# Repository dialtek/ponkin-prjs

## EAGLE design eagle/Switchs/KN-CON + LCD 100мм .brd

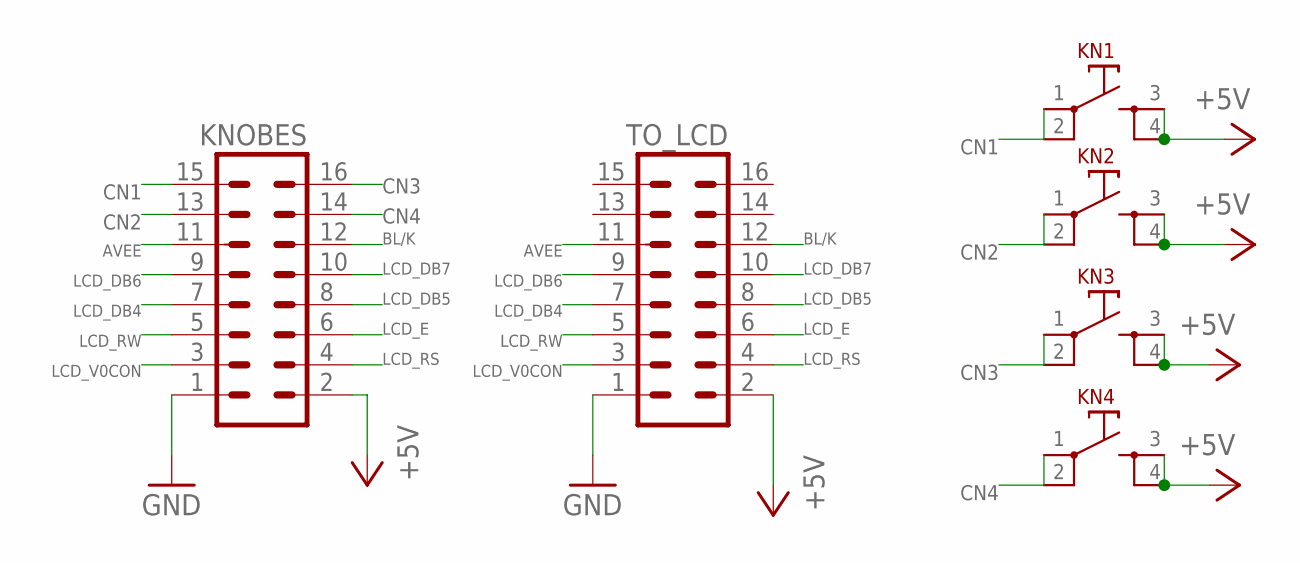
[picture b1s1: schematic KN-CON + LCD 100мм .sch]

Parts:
KN1, KN2, KN3, KN4: LZQ-KN
KNOBES: ML16
TO_LCD: ML16

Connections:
+5V: KN1.3, KN1.4, KN2.3, KN2.4, KN3.3, KN3.4, KN4.3, KN4.4, KNOBES.2, TO_LCD.2
AVEE: KNOBES.11, TO_LCD.11
BL/K: KNOBES.12, TO_LCD.12
CN1: KN1.1, KN1.2, KNOBES.15
CN2: KN2.1, KN2.2, KNOBES.13
CN3: KN3.1, KN3.2, KNOBES.16
CN4: KN4.1, KN4.2, KNOBES.14
GND: KNOBES.1, TO_LCD.1
LCD_DB4: KNOBES.7, TO_LCD.7
LCD_DB5: KNOBES.8, TO_LCD.8
LCD_DB6: KNOBES.9, TO_LCD.9
LCD_DB7: KNOBES.10, TO_LCD.10
LCD_E: KNOBES.6, TO_LCD.6
LCD_RS: KNOBES.4, TO_LCD.4
LCD_RW: KNOBES.5, TO_LCD.5
LCD_V0CON: KNOBES.3, TO_LCD.3

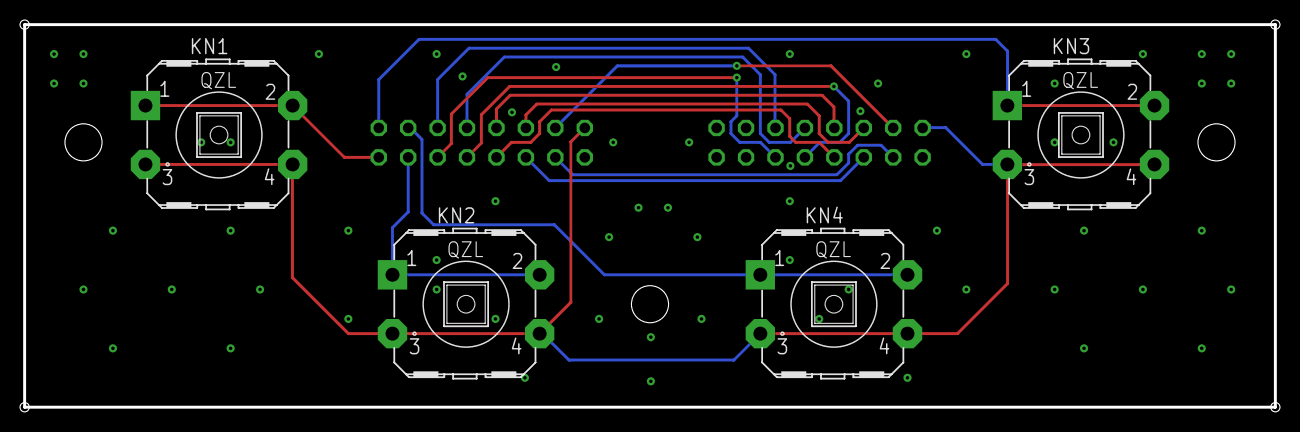
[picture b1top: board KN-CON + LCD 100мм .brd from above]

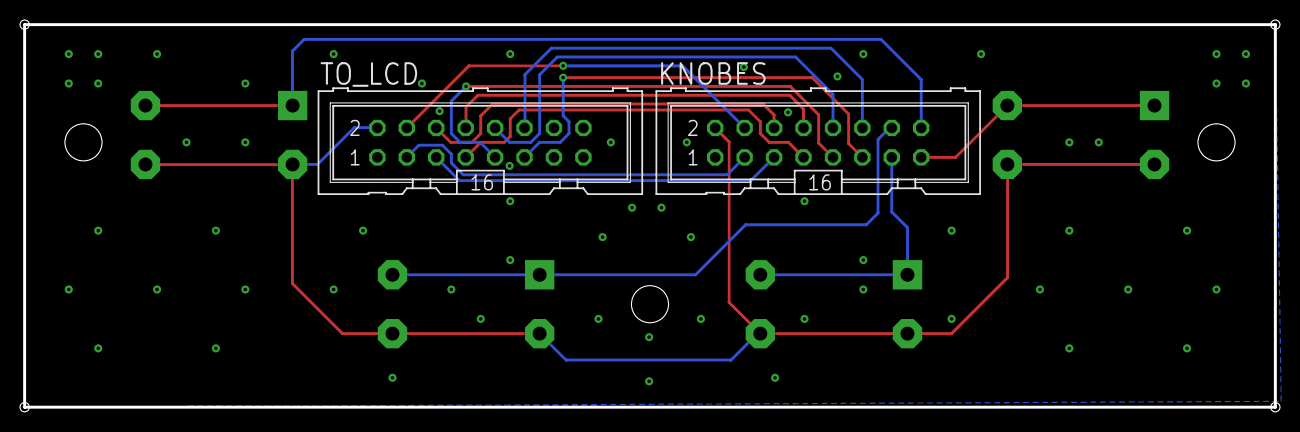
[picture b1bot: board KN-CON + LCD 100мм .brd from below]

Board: 2 copper layers, 108.0 x 33.0 mm, 6 parts (2 on the bottom side), 16 nets.

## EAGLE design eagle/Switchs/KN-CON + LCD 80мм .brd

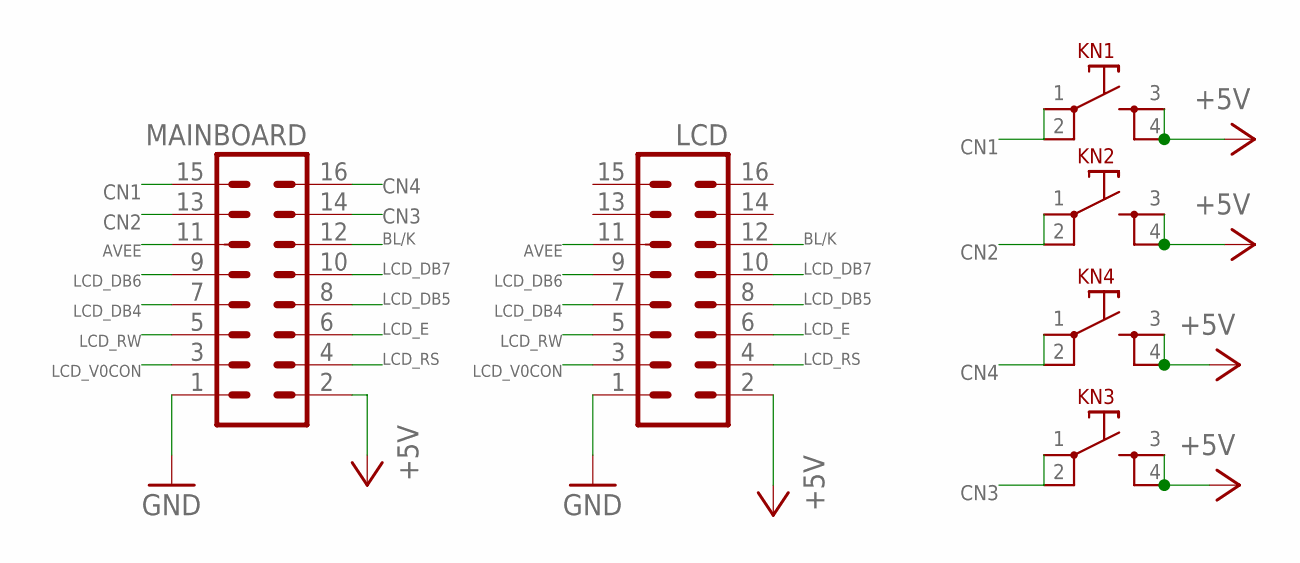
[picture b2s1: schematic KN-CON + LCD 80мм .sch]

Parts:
KN1, KN2, KN3, KN4: LZQ-KN
LCD: ML16
MAINBOARD: ML16

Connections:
+5V: KN1.3, KN1.4, KN2.3, KN2.4, KN3.3, KN3.4, KN4.3, KN4.4, LCD.2, MAINBOARD.2
AVEE: LCD.11, MAINBOARD.11
BL/K: LCD.12, MAINBOARD.12
CN1: KN1.1, KN1.2, MAINBOARD.15
CN2: KN2.1, KN2.2, MAINBOARD.13
CN3: KN3.1, KN3.2, MAINBOARD.14
CN4: KN4.1, KN4.2, MAINBOARD.16
GND: LCD.1, MAINBOARD.1
LCD_DB4: LCD.7, MAINBOARD.7
LCD_DB5: LCD.8, MAINBOARD.8
LCD_DB6: LCD.9, MAINBOARD.9
LCD_DB7: LCD.10, MAINBOARD.10
LCD_E: LCD.6, MAINBOARD.6
LCD_RS: LCD.4, MAINBOARD.4
LCD_RW: LCD.5, MAINBOARD.5
LCD_V0CON: LCD.3, MAINBOARD.3

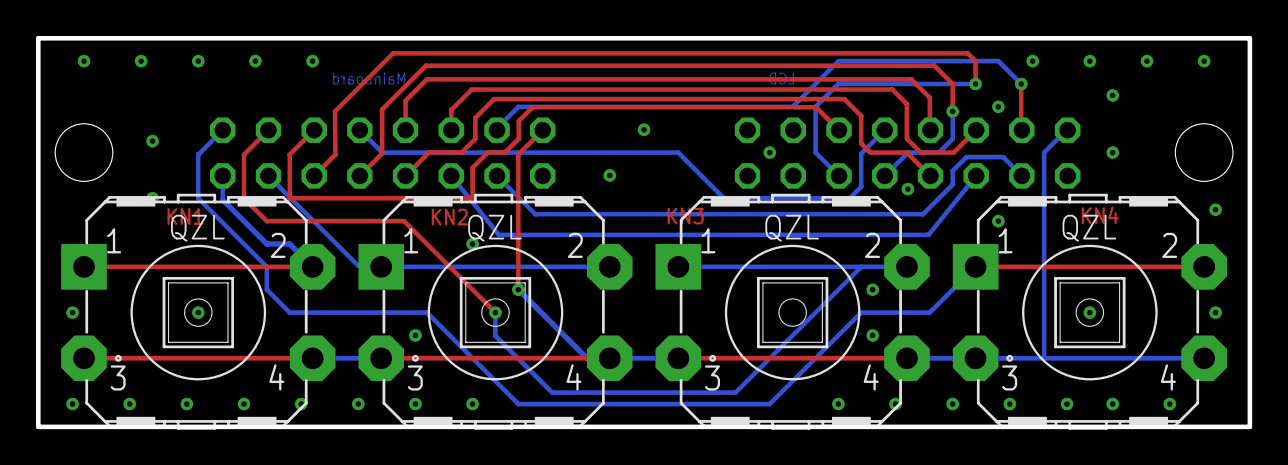
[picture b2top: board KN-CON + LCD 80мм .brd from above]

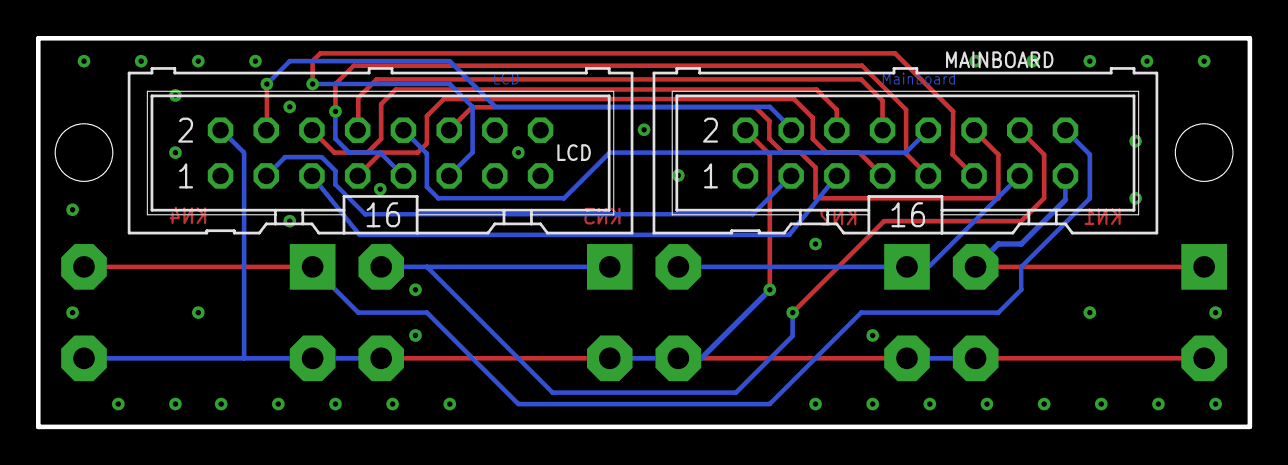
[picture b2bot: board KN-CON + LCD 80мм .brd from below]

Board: 2 copper layers, 67.3 x 21.6 mm, 6 parts (2 on the bottom side), 16 nets.

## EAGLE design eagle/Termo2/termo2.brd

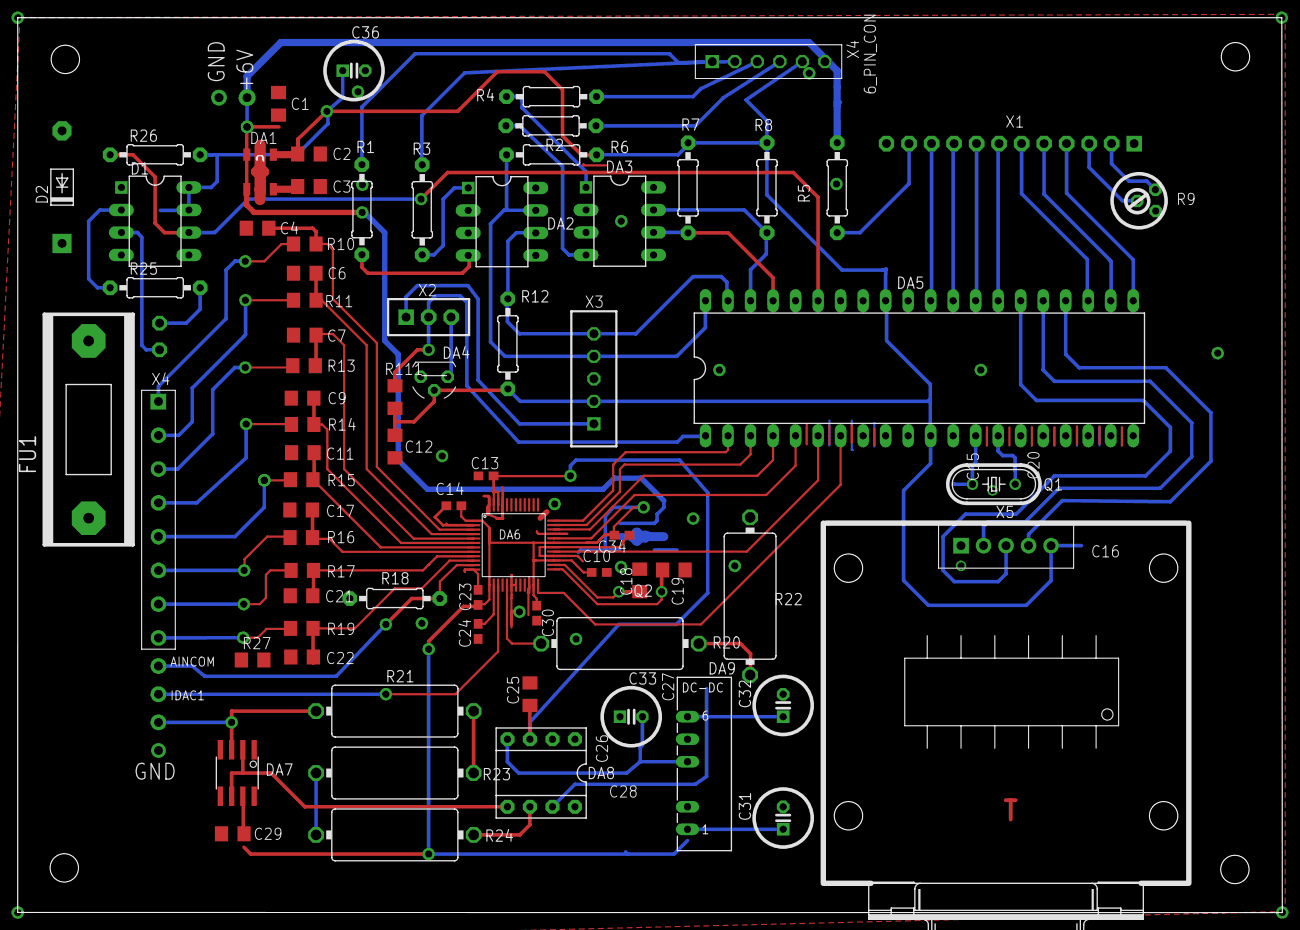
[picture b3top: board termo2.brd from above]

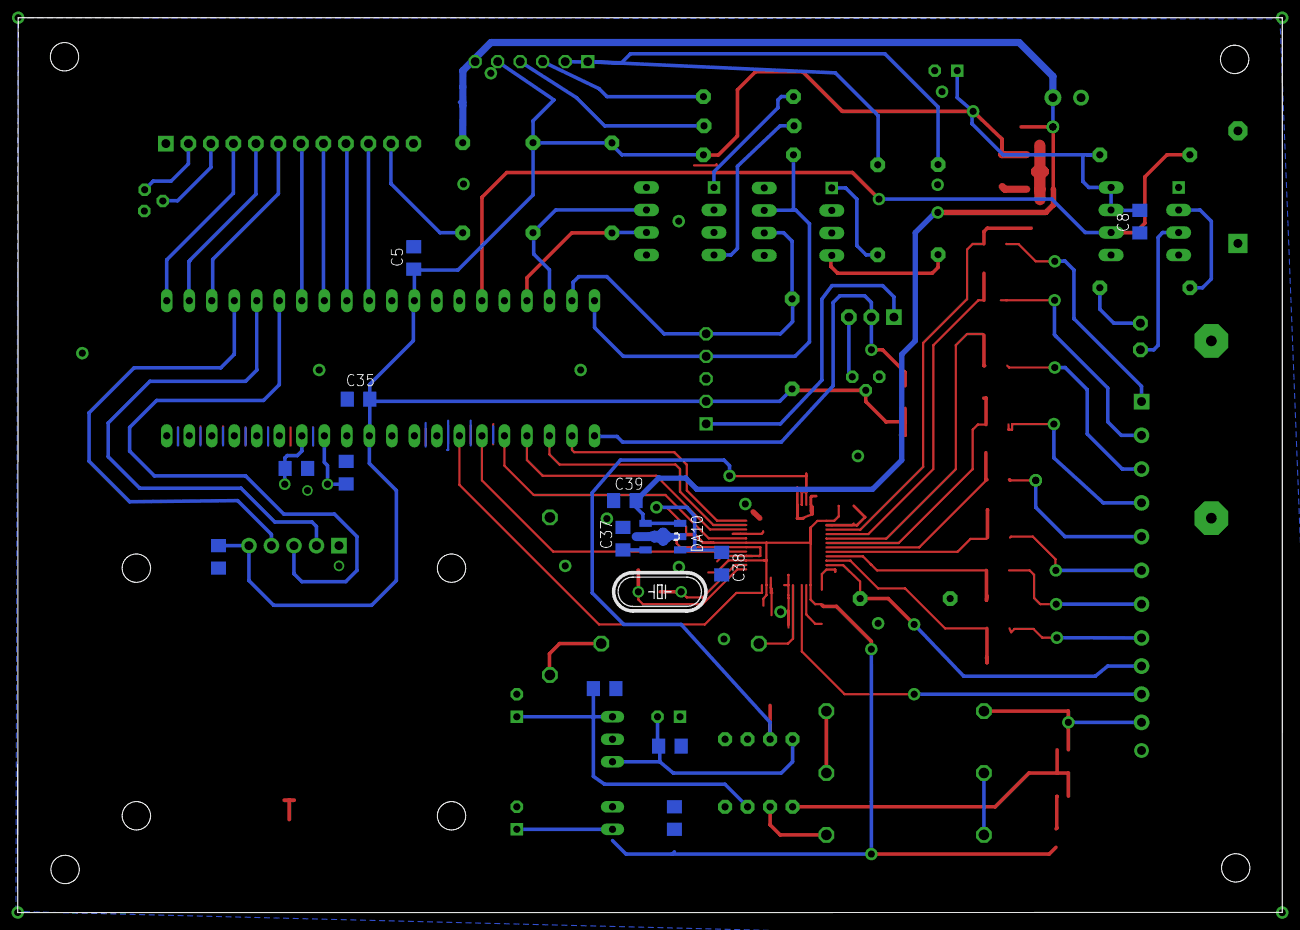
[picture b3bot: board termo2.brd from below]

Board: 2 copper layers, 142.7 x 101.0 mm, 90 parts (14 on the bottom side), 74 nets.

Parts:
8_PIN_1: 8_PIN_CON
C1, C8, C12, C16, C25, C26, C27, C28, C29, C35, C39: 0.1u; C0805D
C2, C38: 1u; C0805D
C3, C37: 0.01u; C0805D
C4: 1n; C0805D
C5, C6, C7, C9, C11, C17, C18, C19, C21, C22: C0805D
C10: C0603
C13, C14, C23, C30, C34: 0.1u; C0603
C15, C20: 12p; C0805D
C24: 1n; C0603
C31, C32, C33, C36: C100MILX6X12
D1: 6N137; DIL08
D2: 1N5061; DO41-10
DA1, DA10: NJM2880; SOT89-5
DA2, DA3: CNY74-H; CNY_DIP8
DA4: DS1811; TO92-60
DA5: PIC18F4320_40; DIL40
DA6: ADS1216ADS1216; ADS1216_PAC
DA7: OPA340U; SO08
DA8: INA128P; DIL08
DA9: NMA
FU1: FUSE5X20
P1, P2: 1_PIN_CON
Q1, Q2: HC49/S
R1, R2, R3, R4, R25: 330; 0207/10
R5, R26: 1k; 0207/10
R6, R7, R8, R12: 4k7; 0207/10
R9: RTRIM3329H
R10: 1k; R0805D
R11, R13, R14, R15, R16, R17, R19: R0805D
R18: 100k; 0207/10
R20, R22: 100k; V235/17
R21, R23, R24: 250k; V235/17
R27, R111: 10k; R0805D
X1: WINSTAR16X4_12
X2: PLC-3PIN
X3: PLC-5PIN
X4: 6_PIN_CON; 6_IN_PINS
X5: KM_RS_232

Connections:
1: DA5.1, R111.P$1, X2.P$2
+5V: C2.1, C5.2, C8.2, C12.2, C16.2, C28.1, C29.1, C31.PLUS, C35.1, C36.PLUS, D1.7, D1.8, DA1.4, DA4.2, DA5.11, DA5.32, DA7.7, DA9.1, R6.2, R7.2, R8.2, R9.2, R12.2, R26.2, R111.P$2, X1.P$2, X3.P$2, X4.P$5, X5.5
+5V_AVDD: C10.2, C14.1, C23.2, C30.1, C34.2, C38.1, DA6.1, DA6.13, DA6.23, DA6.27, DA6.31, DA10.4
+6V: C1.2, C39.2, D2.C, DA1.1, DA1.5, DA10.1, DA10.5, FU1.P$2, R5.1
AINCOM: DA6.11, R18.1
DB4: DA5.27, X1.P$7
DB5: DA5.28, X1.P$8
DB6: DA5.29, X1.P$9
DB7: DA5.30, X1.P$10
DRDY: DA5.5, DA6.32
DSYNC: DA5.6, DA6.29
D_IN: DA5.3, DA6.35
D_OUT: DA5.2, DA6.36
E: DA5.23, X1.P$6
IN1.1: C4.1, DA6.3, R10.P$1
IN1.2: C6.1, DA6.4, R11.P$1
IN2.1: C7.1, DA6.5, R13.P$1
IN2.2: C9.1, DA6.6, R14.P$1
IN3.1: C11.1, DA6.7, R15.P$1
IN3.2: C17.1, DA6.8, R16.P$1
IN4.1: C21.1, DA6.9, R17.P$1
IN4.2: C22.1, DA6.10, R19.P$1
INA_OUT: DA7.3, R21.1
K2: R1.2, X4.P$2
K3: R4.1, X4.P$3
K4: R2.2, X4.P$4
KN1,PGD: DA2.7, DA5.40, R6.1, X3.P$4
KN2,PGC: DA2.6, DA5.39, R12.1, X3.P$5
KN3: DA3.7, DA5.38, R8.1
KN4: DA3.6, DA5.37, R7.1
MCLR: X2.P$1, X3.P$1
unnamed: C15.2, DA5.13, Q1.1
unnamed: C20.2, DA5.14, Q1.2
unnamed: DA2.4, R1.1
unnamed: C3.1, DA1.3
unnamed: C24.2, DA6.14
unnamed: DA4.1, X2.P$3
unnamed: C19.2, DA6.25, Q2.2
unnamed: C18.2, DA6.26, Q2.1
unnamed: 8_PIN_1.P$6, R16.P$2
unnamed: 8_PIN_1.P$1, R10.P$2
unnamed: 8_PIN_1.P$2, R11.P$2
unnamed: 8_PIN_1.P$7, R17.P$2
unnamed: DA3.1, R4.2
unnamed: 8_PIN_1.P$8, R19.P$2, R27.P$1
unnamed: DA3.4, R2.1
unnamed: R5.2, X1.P$11
unnamed: 8_PIN_1.P$5, R15.P$2
unnamed: C27.1, C32.PLUS, DA8.7, DA9.6
unnamed: 8_PIN_1.P$3, R13.P$2
unnamed: 8_PIN_1.P$4, R14.P$2
unnamed: DA7.2, DA7.6, DA8.5
unnamed: DA8.6, R24.2
unnamed: C26.1, C33.MINUS, DA8.4, DA9.4
unnamed: DA5.26, X5.3
unnamed: DA5.25, X5.2
unnamed: DA5.24, X5.4
unnamed: R23.2, R24.1
unnamed: R21.2, R23.1
unnamed: DA6.17, R20.1
unnamed: R20.2, R22.1
unnamed: C37.1, DA10.3
unnamed: D1.6, DA5.35, R26.1
unnamed: D1.2, R25.1
unnamed: D1.3, P2.P$1
unnamed: P1.P$1, R25.2
PE: C1.1, C2.2, C3.2, C4.2, C5.1, C6.2, C7.2, C8.1, C9.2, C10.1, C11.2, C12.1, C13.2, C14.2, C15.1, C16.1, C17.2, C18.1, C19.1, C20.1, C21.2, C22.2, C23.1, C24.1, C25.2, C26.2, C27.2, C28.2, C29.2, C30.2, C31.MINUS, C32.MINUS, C33.PLUS, C34.1, C35.2, C36.MINUS, C37.2, C38.2, C39.1, D1.5, D2.A, DA1.2, DA1.21, DA2.2, DA2.3, DA2.5, DA2.8, DA3.2, DA3.3, DA3.5, DA3.8, DA4.3, DA5.12, DA5.31, DA6.2, DA6.12, DA6.18, DA6.19, DA6.20, DA6.21, DA6.22, DA6.28, DA6.30, DA6.45, DA6.48, DA7.4, DA8.2, DA9.2, DA9.5, DA10.2, DA10.21, R9.1, R18.2, R22.2, R27.P$2, X1.P$1, X1.P$12, X3.P$3, X4.P$6, X5.1
R15: DA2.1, R3.2
REF: C13.1, C25.1, DA6.46, DA6.47, DA8.3
RESET: DA5.7, DA6.24
RS: DA5.21, X1.P$4
RW: DA5.22, X1.P$5
SCLK: DA5.4, DA6.34
V0CON: R9.3, X1.P$3

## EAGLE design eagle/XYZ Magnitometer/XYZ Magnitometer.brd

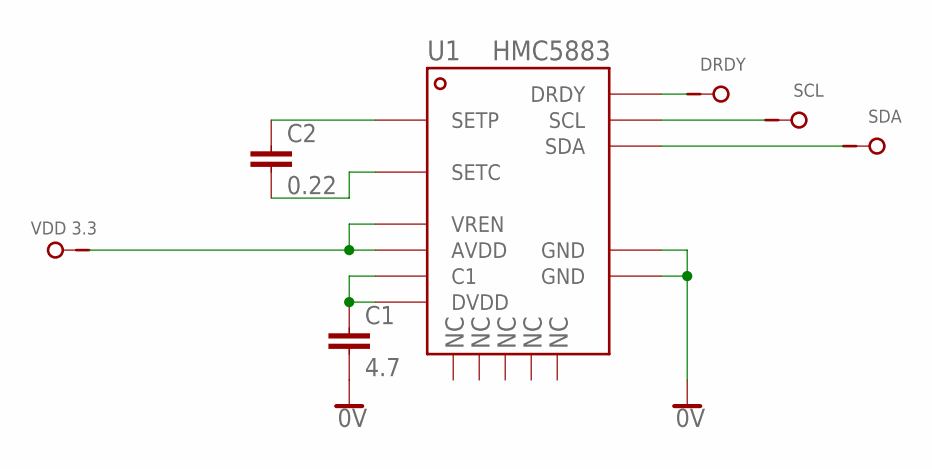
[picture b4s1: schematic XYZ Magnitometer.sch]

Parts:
C1: 4.7; C1206K
C2: 0.22; C0805K
P1: SDA; 1_PIN_PLANAR
P2: VDD 3.3; 1_PIN_PLANAR
P3: SCL; 1_PIN_PLANAR
P5: DRDY; 1_PIN_PLANAR
U1: HMC5883; QFN16-4X4

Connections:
0V: C1.2, U1.P$9 (GND), U1.P$11 (GND)
1: U1.P$3 (1)
2: U1.P$4 (2)
3: U1.P$5 (3)
4: U1.P$6 (4)
5: U1.P$7 (5)
unnamed: C1.1, U1.P$10 (C1), U1.P$13 (DVDD)
unnamed: C2.1, U1.P$8 (SETP)
unnamed: C2.2, U1.P$12 (SETC)
unnamed: P2.P$1, U1.P$2 (AVDD), U1.P$14 (VREN)
unnamed: P3.P$1, U1.P$1 (SCL)
unnamed: P1.P$1, U1.P$16 (SDA)
unnamed: P5.P$1, U1.P$15 (DRDY)

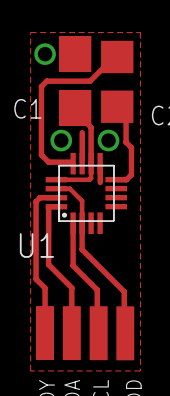
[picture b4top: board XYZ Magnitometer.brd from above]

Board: 2 copper layers, 7 parts (0 on the bottom side), 8 nets.

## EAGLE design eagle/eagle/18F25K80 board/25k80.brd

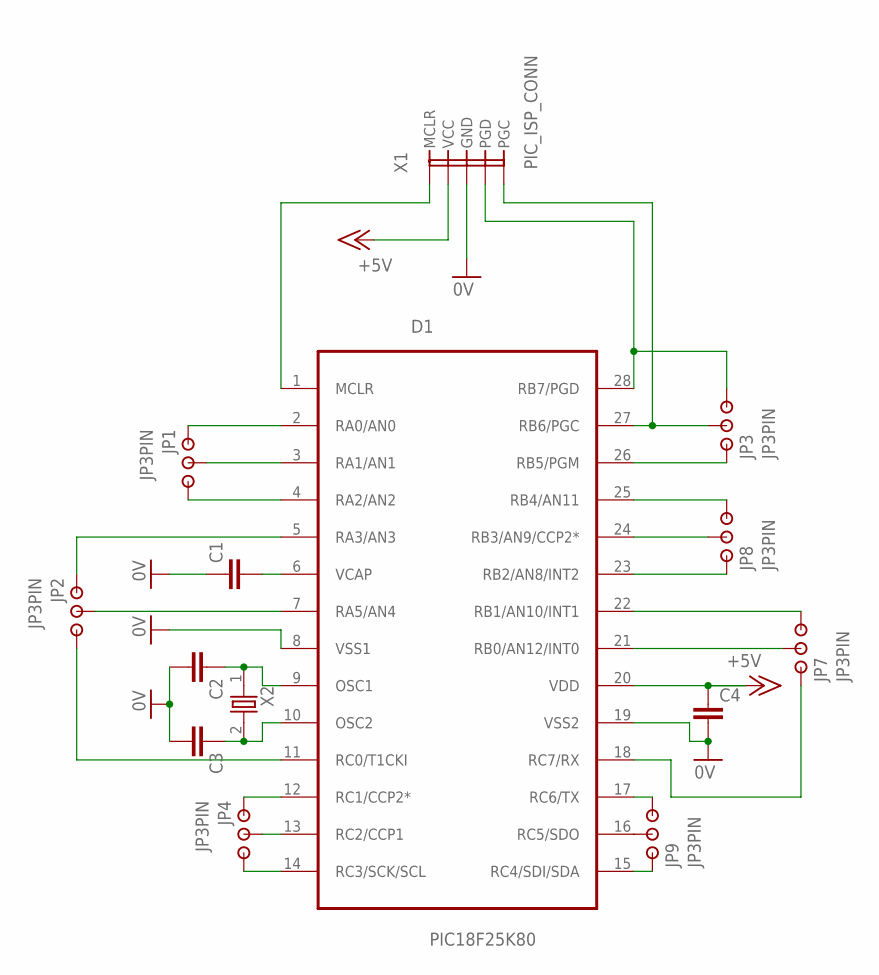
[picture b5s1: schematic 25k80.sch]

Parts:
C1, C2, C3, C4: C0805; C0805D
D1: PIC18F25K80; SO-28W
JP1, JP2, JP3, JP4, JP7, JP8, JP9: JP3PIN; PLC-3PIN
X1: PIC_ISP_CONN; PLC-5PIN
X2: HC49/S

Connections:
0V: C1.1, C2.2, C3.2, C4.2, D1.8 (VSS1), D1.19 (VSS2), X1.P$3 (GND)
+5V: C4.1, D1.20 (VDD), X1.P$2 (VCC)
unnamed: D1.28 (RB7/PGD), JP3.P$3, X1.P$4 (PGD)
unnamed: D1.27 (RB6/PGC), JP3.P$2, X1.P$5 (PGC)
unnamed: D1.1 (MCLR), X1.P$1 (MCLR)
unnamed: C1.2, D1.6 (VCAP)
unnamed: D1.2 (RA0/AN0), JP1.P$1
unnamed: D1.3 (RA1/AN1), JP1.P$2
unnamed: D1.4 (RA2/AN2), JP1.P$3
unnamed: D1.5 (RA3/AN3), JP2.P$1
unnamed: D1.7 (RA5/AN4), JP2.P$2
unnamed: D1.25 (RB4/AN11), JP8.P$3
unnamed: D1.26 (RB5/PGM), JP3.P$1
unnamed: C2.1, D1.9 (OSC1), X2.1
unnamed: C3.1, D1.10 (OSC2), X2.2
unnamed: D1.24 (RB3/AN9/CCP2*), JP8.P$2
unnamed: D1.23 (RB2/AN8/INT2), JP8.P$1
unnamed: D1.22 (RB1/AN10/INT1), JP7.P$3
unnamed: D1.21 (RB0/AN12/INT0), JP7.P$2
unnamed: D1.11 (RC0/T1CKI), JP2.P$3
unnamed: D1.18 (RC7/RX), JP7.P$1
unnamed: D1.16 (RC5/SDO), JP9.P$2
unnamed: D1.17 (RC6/TX), JP9.P$3
unnamed: D1.15 (RC4/SDI/SDA), JP9.P$1
unnamed: D1.14 (RC3/SCK/SCL), JP4.P$3
unnamed: D1.13 (RC2/CCP1), JP4.P$2
unnamed: D1.12 (RC1/CCP2*), JP4.P$1

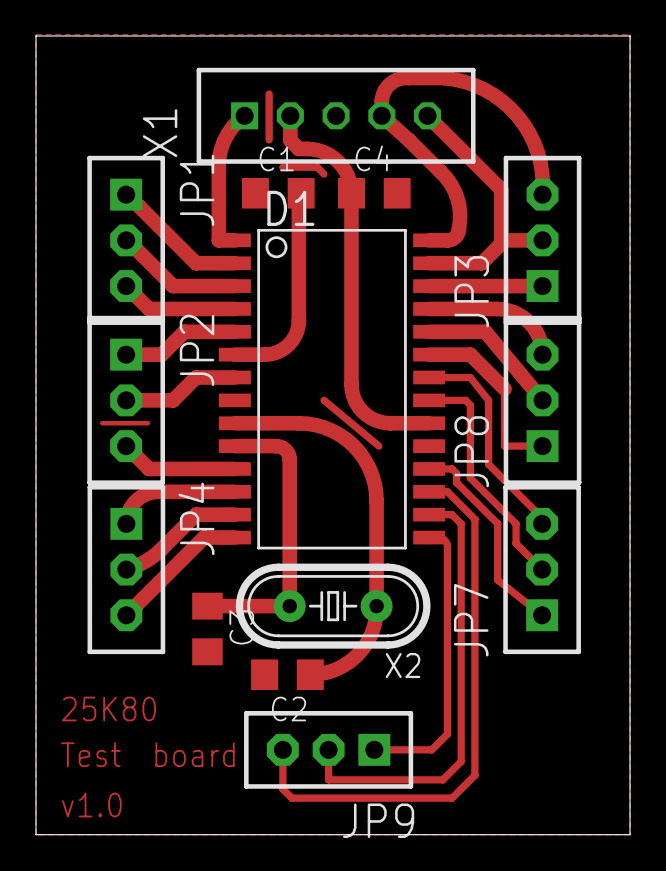
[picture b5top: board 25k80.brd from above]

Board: 2 copper layers, 33.0 x 44.4 mm, 14 parts (0 on the bottom side), 27 nets.

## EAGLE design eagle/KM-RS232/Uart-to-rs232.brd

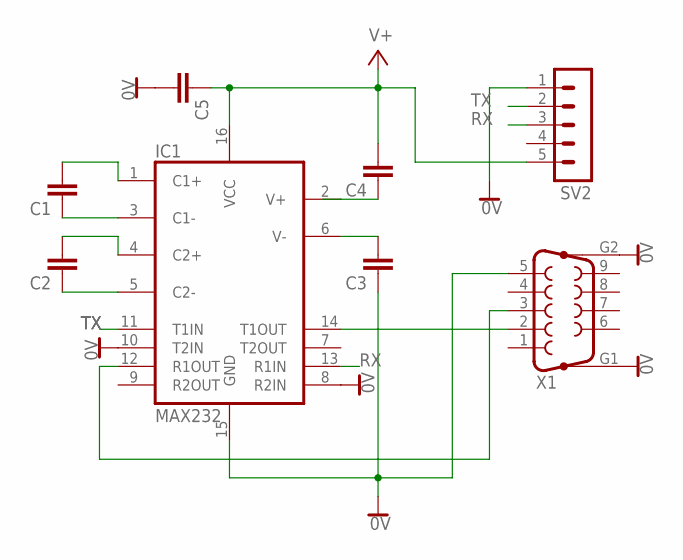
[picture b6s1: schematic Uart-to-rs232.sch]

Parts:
C1, C2, C3, C4, C5: C0805; C0805D
IC1: MAX232; DIL16
SV2: MA05-1
X1: F09HP

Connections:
0V: C3.1, C5.2, IC1.8 (R2IN), IC1.10 (T2IN), IC1.15 (GND), SV2.1, X1.5, X1.G1, X1.G2
+5V: C4.2, C5.1, IC1.16 (VCC), SV2.5
unnamed: IC1.14 (T1OUT), X1.2
unnamed: C1.2, IC1.1 (C1+)
unnamed: C1.1, IC1.3 (C1-)
unnamed: C2.2, IC1.4 (C2+)
unnamed: C2.1, IC1.5 (C2-)
unnamed: C3.2, IC1.6 (V-)
unnamed: C4.1, IC1.2 (V+)
unnamed: IC1.12 (R1OUT), X1.3
RX: IC1.13 (R1IN), SV2.3
TX: IC1.11 (T1IN), SV2.2

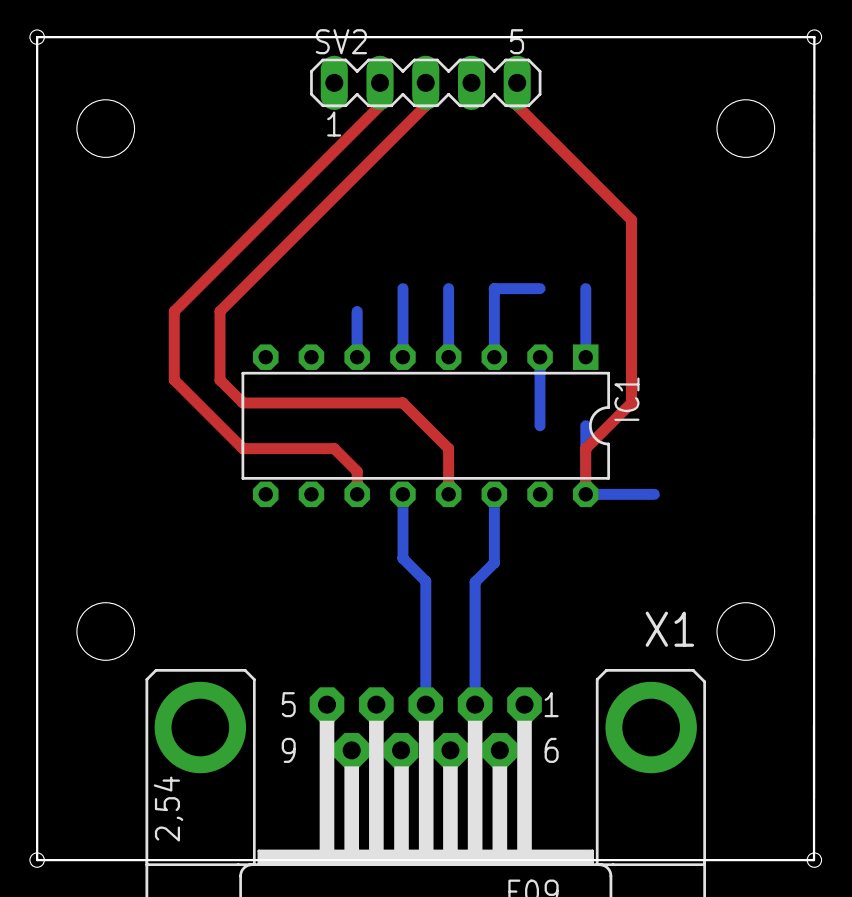
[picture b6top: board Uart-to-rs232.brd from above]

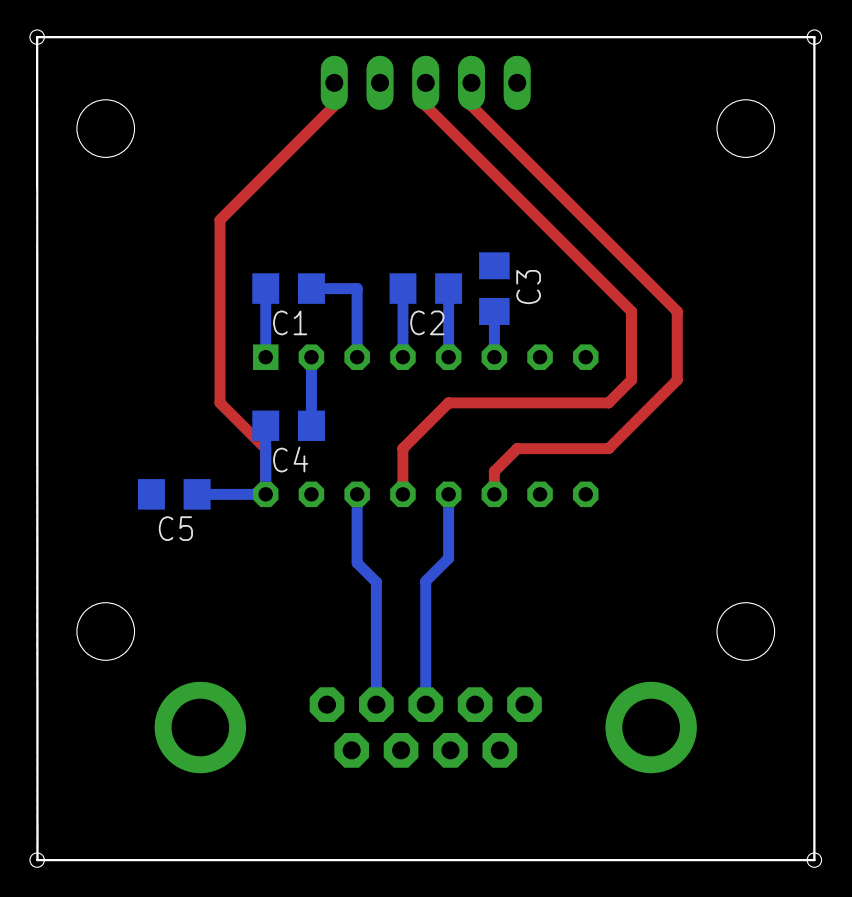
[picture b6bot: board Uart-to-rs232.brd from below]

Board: 2 copper layers, 43.2 x 45.7 mm, 8 parts (5 on the bottom side), 12 nets.

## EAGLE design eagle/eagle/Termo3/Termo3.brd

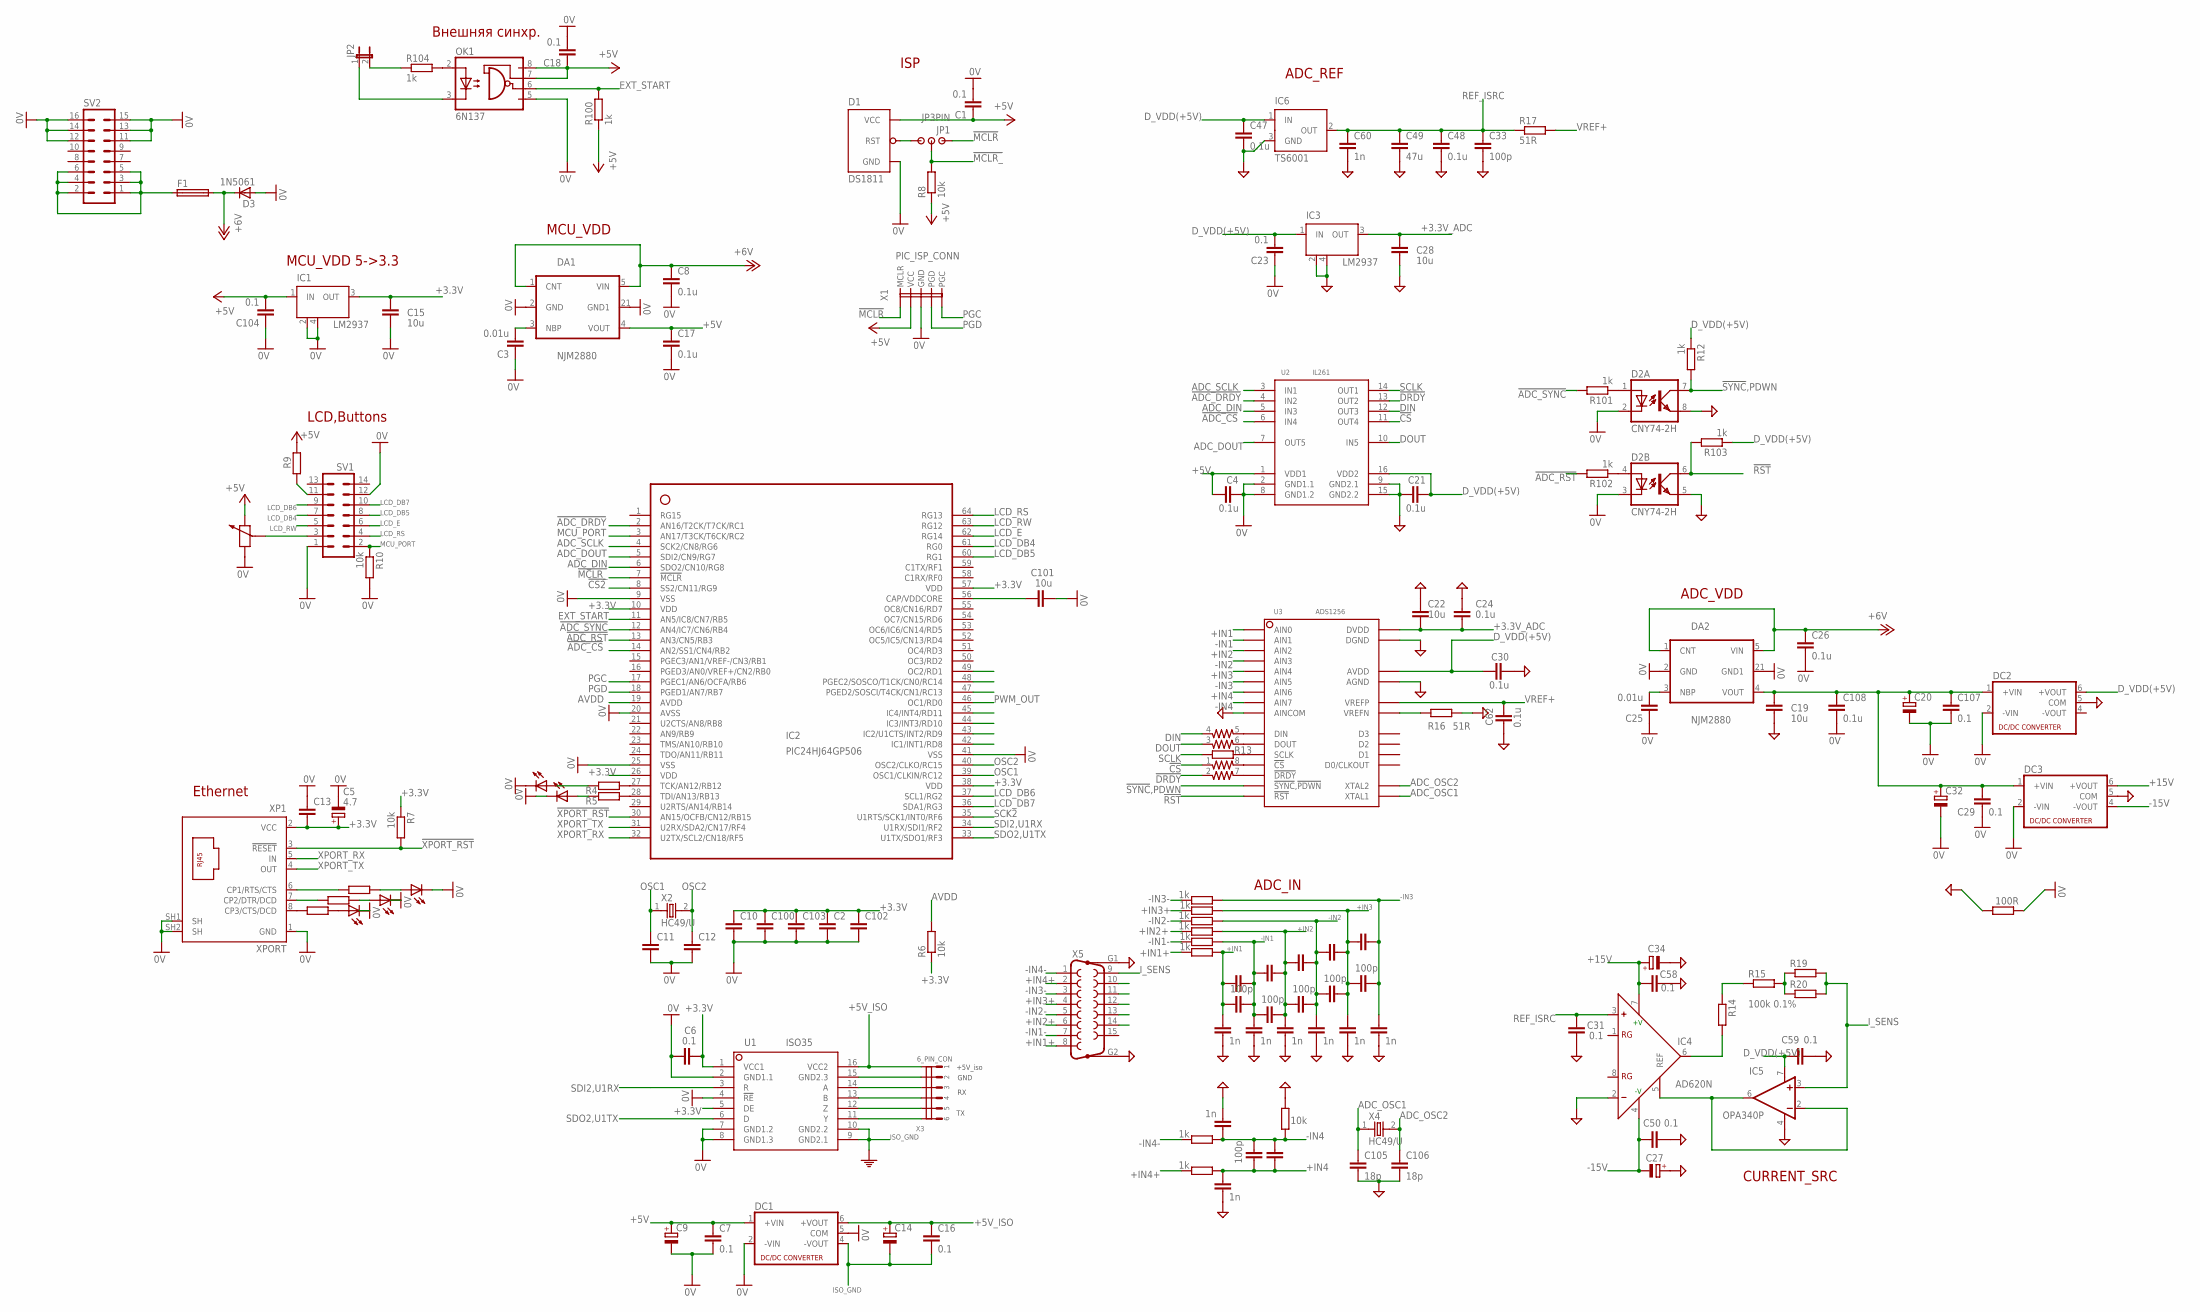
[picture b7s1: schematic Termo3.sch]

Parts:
C1, C6, C7, C16, C18, C23, C29, C31, C50, C58, C59, C104, C107: 0.1; C0805D
C2, C10, C11, C12, C13, C100, C102, C103: C0805; C0805D
C3, C25: 0.01u; C0805D
C4, C8, C17, C21, C24, C26, C30, C47, C48, C62, C108: 0.1u; C0805D
C5: 4.7; C100MILX6X12
C9, C14, C20, C27, C32, C34: C100MFX25V; C100MILX6X12
C15, C19, C22, C28, C101: 10u; C0805D
C33, C35, C36, C37, C38, C39, C40: 100p; C0805D
C41, C42, C43, C44, C45, C46, C51, C52, C53, C54, C55, C56, C57, C60, C61: 1n; C0805D
C49: 47u; C0805D
C105, C106: 18p; C0805D
D1: DS1811; TO92-60
D2: CNY74-2H; DIL08
D3: 1N5061; DO41-10
DA1, DA2: NJM2880; SOT89-5
DC1, DC2, DC3: NMA
F1: TE5
HL1, HL2, HL3, HL4, HL5: LED3MM
IC1, IC3: LM2937; SOT223
IC2: PIC24HJ64GP506; TQFP64-10X10
IC4: AD620N; DIL08
IC5: OPA340P; DIL08
IC6: TS6001; SOT23
JP1: JP3PIN; PLC-3PIN
JP2: JP1E; JP1
OK1: 6N137; DIL08
POT1: RTRIM3329H
R1, R2, R3, R12, R21, R22, R23, R24, R25, R26, R27, R28, R100, R101, R102, R103, R104: 1k; R0805D
R4, R5, R13, R16, R17: 51R; R0805D
R6, R7, R8, R10, R18: 10k; R0805D
R9, R14, R19, R20: MLT025"; 0207/10
R11: 100R; R0805D
R15: 100k 0.1%; 0207/10
RN1: 742-8_SNS; 742-8NS
SV1: ML14
SV2: MA08-2W
U1: ISO35; ISO35_SOIC16
U2: IL261; SOIC-16
U3: ADS1256; PCM2705-TSSOP28
X1: PIC_ISP_CONN; PLC-5PIN
X2, X4: HC49/U; HC49U-V
X3: 6_PIN_CON; 6_IN_PINS
X5: F15HP
XP1: XPORT

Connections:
0V: C1.2, C2.2, C3.1, C4.2, C5.MINUS (-), C6.1, C7.2, C8.2, C9.MINUS (-), C10.2, C11.2, C12.2, C13.1, C15.1, C17.2, C18.2, C20.MINUS (-), C23.1, C25.1, C26.2, C29.1, C32.MINUS (-), C100.2, C101.2, C102.2, C103.2, C104.1, C107.2, C108.2, D1.3 (GND), D2.2 (C), D2.3 (C), D3.A, DA1.2 (GND), DA1.21 (GND1), DA2.2 (GND), DA2.21 (GND1), DC1.2 (-VIN), DC1.5 (COM), DC2.2 (-VIN), DC3.2 (-VIN), HL1.K (C), HL2.K (C), HL3.K (C), HL4.K (C), HL5.K (C), IC1.2 (GND), IC1.4 (GND), IC2.9 (VSS), IC2.20 (AVSS), IC2.25 (VSS), IC2.41 (VSS), OK1.5 (GND), POT1.1, R10.P$2 (2), R11.P$1 (1), SV1.1, SV1.12, SV2.11, SV2.12, SV2.13, SV2.14, SV2.15, SV2.16, U1.2 (GND1.1), U1.4 (!RE), U1.7 (GND1.2), U1.8 (GND1.3), U2.2 (GND1.1), U2.8 (GND1.2), X1.P$3 (GND), XP1.1 (GND), XP1.SH1 (SH), XP1.SH2 (SH)
!ADC_CS: IC2.14 (AN2/SS1/CN4/RB2), U2.6 (IN4)
!ADC_DRDY: IC2.2 (AN16/T2CK/T7CK/RC1), U2.4 (IN2)
!ADC_RST: IC2.13 (AN3/CN5/RB3), R102.P$2 (2)
!ADC_SYNC: IC2.12 (AN4/IC7/CN6/RB4), R101.P$2 (2)
!CS: RN1.1, U2.11 (OUT4)
!CS2: IC2.8 (SS2/CN11/RG9)
!DRDY: RN1.2 (1), U2.13 (OUT2)
!MCLR: JP1.P$1, X1.P$1 (MCLR)
!MCLR_: IC2.7 (!MCLR), JP1.P$2, R8.P$2 (2)
!RST: D2.6 (COL), R103.P$2 (2), U3.15 (!RST)
!SYNC,PDWN: D2.7 (COL), R12.P$2 (2), U3.14 (!SYNC,!PDWN)
!XPORT_RST: IC2.30 (AN15/OCFB/CN12/RB15), R7.P$2 (2), XP1.3 (!RESET)
+3.3V: C2.1, C5.PLUS (+), C6.2, C10.1, C13.2, C15.2, C100.1, C102.1, C103.1, IC1.3 (OUT), IC2.10 (VDD), IC2.26 (VDD), IC2.38 (VDD), IC2.57 (VDD), R6.P$1 (1), R7.P$1 (1), U1.1 (VCC1), U1.5 (DE), XP1.2 (VCC)
+3.3V_ADC: C22.2, C24.1, C28.2, IC3.3 (OUT), U3.16 (DVDD)
+5V: C1.1, C4.1, C7.1, C9.PLUS (+), C17.1, C18.1, C104.2, D1.2 (VCC), DA1.4 (VOUT), DC1.1 (+VIN), IC1.1 (IN), OK1.7 (VE), OK1.8 (VCC), POT1.2, R8.P$1 (1), R9.2, R100.P$1 (1), U2.1 (VDD1), X1.P$2 (VCC)
+5V_ISO: C14.PLUS (+), C16.1, DC1.6 (+VOUT), U1.16 (VCC2), X3.P$1 (1)
+6V: C8.1, C26.1, D3.C, DA1.1 (CNT), DA1.5 (VIN), DA2.1 (CNT), DA2.5 (VIN), F1.2
+15V: C34.PLUS (+), C58.2, DC3.6 (+VOUT), IC4.7 (+V)
+IN1: C40.1, C46.1, C57.1, R28.P$1 (1), U3.6 (AIN0)
+IN1+: R28.P$2 (2), X5.8
+IN2: C38.1, C39.2, C44.1, C45.2, C55.1, R26.P$1 (1), U3.8 (AIN2)
+IN2+: R26.P$2 (2), X5.6
+IN3: C36.1, C37.2, C42.1, C43.2, C53.1, R24.P$1 (1), U3.10 (AIN4)
+IN3+: R24.P$2 (2), X5.4
+IN4: C35.1, C41.1, C51.1, R22.P$1 (1), U3.12 (AIN6)
+IN4+: R22.P$2 (2), X5.2
-15V: C27.MINUS (-), C50.2, DC3.4 (-VOUT), IC4.4 (-V)
-IN1: C39.1, C40.2, C45.1, C46.2, C56.1, R27.P$1 (1), U3.7 (AIN1)
-IN1-: R27.P$2 (2), X5.7
-IN2: C37.1, C38.2, C43.1, C44.2, C54.1, R25.P$1 (1), U3.9 (AIN3)
-IN2-: R25.P$2 (2), X5.5
-IN3: C36.2, C42.2, C52.1, R23.P$1 (1), U3.11 (AIN5)
-IN3-: R23.P$2 (2), X5.3
-IN4: C35.2, C41.2, C61.1, R18.P$2 (2), R21.P$1 (1), U3.13 (AIN7)
-IN4-: R21.P$2 (2), X5.1
ADC_AVDD: C19.2, C20.PLUS (+), C29.2, C32.PLUS (+), C107.1, C108.1, DA2.4 (VOUT), DC2.1 (+VIN), DC3.1 (+VIN)
ADC_DIN: IC2.6 (SDO2/CN10/RG8), U2.5 (IN3)
ADC_DOUT: IC2.5 (SDI2/CN9/RG7), U2.7 (OUT5)
ADC_OSC1: C105.1, U3.19 (XTAL1), X4.1
ADC_OSC2: C106.1, U3.18 (XTAL2), X4.2
ADC_SCLK: IC2.4 (SCK2/CN8/RG6), U2.3 (IN1)
AVDD: IC2.19 (AVDD), R6.P$2 (2)
DGND: C19.1, C21.1, C22.1, C24.2, C27.PLUS (+), C28.1, C30.2, C31.2, C33.2, C34.MINUS (-), C47.2, C48.2, C49.2, C50.1, C51.2, C52.2, C53.2, C54.2, C55.2, C56.2, C57.2, C58.1, C59.2, C60.2, C61.2, C62.1, C105.2, C106.2, D2.5 (EMIT), D2.8 (EMIT), DC2.5 (COM), DC3.5 (COM), IC3.2 (GND), IC3.4 (GND), IC4.2 (-), IC5.4 (V-), IC6.3 (GND), R11.P$2 (2), R16.P$2 (2), R18.P$1 (1), U2.9 (GND2.1), U2.15 (GND2.2), U3.2 (AGND), U3.5 (AINCOM), U3.17 (DGND), X5.G1, X5.G2
DIN: RN1.4 (1), U2.12 (OUT3)
DOUT: RN1.3 (1), U2.10 (IN5)
D_VDD(+5V): C21.2, C30.1, C47.1, C59.1, DC2.6 (+VOUT), IC3.1 (IN), IC5.7 (V+), IC6.1 (IN), R12.P$1 (1), R103.P$1 (1), U2.16 (VDD2), U3.1 (AVDD)
EXT_START: IC2.11 (AN5/IC8/CN7/RB5), OK1.6 (VO), R100.P$2 (2)
ISO_GND: C14.MINUS (-), C16.2, DC1.4 (-VOUT), U1.9 (GND2.1), U1.10 (GND2.2), U1.15 (GND2.3), X3.P$2 (2)
I_SENS: IC5.3 (+IN), R19.2, R20.2, X5.9
LCD_DB4: IC2.61 (RG0), SV1.7
LCD_DB5: IC2.60 (RG1), SV1.8
LCD_DB6: IC2.37 (SCL1/RG2), SV1.9
LCD_DB7: IC2.36 (SDA1/RG3), SV1.10
LCD_E: IC2.62 (RG14), SV1.6
LCD_RS: IC2.64 (RG13), SV1.4
LCD_RW: IC2.63 (RG12), SV1.5
MCU_PORT: IC2.3 (AN17/T3CK/T6CK/RC2), R10.P$1 (1), SV1.2
unnamed: C101.1, IC2.56 (CAP/VDDCORE)
unnamed: D1.1 (RST), JP1.P$3
unnamed: RN1.8 (2), U3.20 (!CS)
unnamed: RN1.7 (2), U3.21 (!DRDY)
unnamed: RN1.6 (2), U3.22 (DOUT)
unnamed: RN1.5 (2), U3.23 (DIN)
unnamed: R13.P$2 (2), U3.24 (SCLK)
unnamed: D2.1 (A), R101.P$1 (1)
unnamed: IC4.5 (REF), IC5.2 (-IN), IC5.6 (OUT)
unnamed: C25.2, DA2.3 (NBP)
unnamed: D2.4 (A), R102.P$1 (1)
unnamed: C3.2, DA1.3 (NBP)
unnamed: IC4.6 (OUT), R14.2
unnamed: POT1.3, SV1.3
unnamed: R9.1, SV1.11
unnamed: IC2.28 (TDI/AN13/RB13), R5.P$1 (1)
unnamed: HL2.A, R5.P$2 (2)
unnamed: JP2.1, OK1.3 (C)
unnamed: HL3.A, R1.P$2 (2)
unnamed: R1.P$1 (1), XP1.6 (CP1/RTS/CTS)
unnamed: R2.P$1 (1), XP1.7 (CP2/DTR/DCD)
unnamed: R3.P$1 (1), XP1.8 (CP3/CTS/DCD)
unnamed: HL4.A, R2.P$2 (2)
unnamed: HL5.A, R3.P$2 (2)
unnamed: OK1.2 (A), R104.P$2 (2)
unnamed: JP2.2, R104.P$1 (1)
unnamed: F1.1, SV2.1, SV2.2, SV2.3, SV2.4, SV2.5, SV2.6
unnamed: IC2.27 (TCK/AN12/RB12), R4.P$1 (1)
unnamed: R14.1, R15.1
unnamed: R16.P$1 (1), U3.3 (VREFN)
unnamed: R15.2, R19.1, R20.1
unnamed: U1.14 (A), X3.P$3 (3)
unnamed: HL1.A, R4.P$2 (2)
unnamed: U1.13 (B), X3.P$4 (4)
unnamed: U1.12 (Z), X3.P$5 (5)
unnamed: U1.11 (Y), X3.P$6 (6)
OSC1: C11.1, IC2.39 (OSC1/CLKIN/RC12), X2.1
OSC2: C12.1, IC2.40 (OSC2/CLKO/RC15), X2.2
PGC: IC2.17 (PGEC1/AN6/OCFA/RB6), X1.P$5 (PGC)
PGD: IC2.18 (PGED1/AN7/RB7), X1.P$4 (PGD)
PWM_OUT: IC2.46 (OC1/RD0)
REF_ISRC: C31.1, C33.1, C48.1, C49.1, C60.1, IC4.3 (+), IC6.2 (OUT), R17.P$1 (1)
SCK2: IC2.35 (U1RTS/SCK1/INT0/RF6)
SCLK: R13.P$1 (1), U2.14 (OUT1)
SDI2,U1RX: IC2.34 (U1RX/SDI1/RF2)
SDO2,U1TX: IC2.33 (U1TX/SDO1/RF3), U1.6 (D)
VREF+: C62.2, R17.P$2 (2), U3.4 (VREFP)
XPORT_RX: IC2.32 (U2TX/SCL2/CN18/RF5), XP1.5 (IN)
XPORT_TX: IC2.31 (U2RX/SDA2/CN17/RF4), XP1.4 (OUT)

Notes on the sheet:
ADC_VDD
MCU_VDD
Внешняя синхр.
MCU_VDD 5->3.3
ISP
Ethernet
LCD,Buttons
ADC_IN
CURRENT_SRC
ADC_REF
+5V_iso
GND

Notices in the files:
parts and their libraries:
resistor-array: Copyright (C) 2008, Bob Starr
